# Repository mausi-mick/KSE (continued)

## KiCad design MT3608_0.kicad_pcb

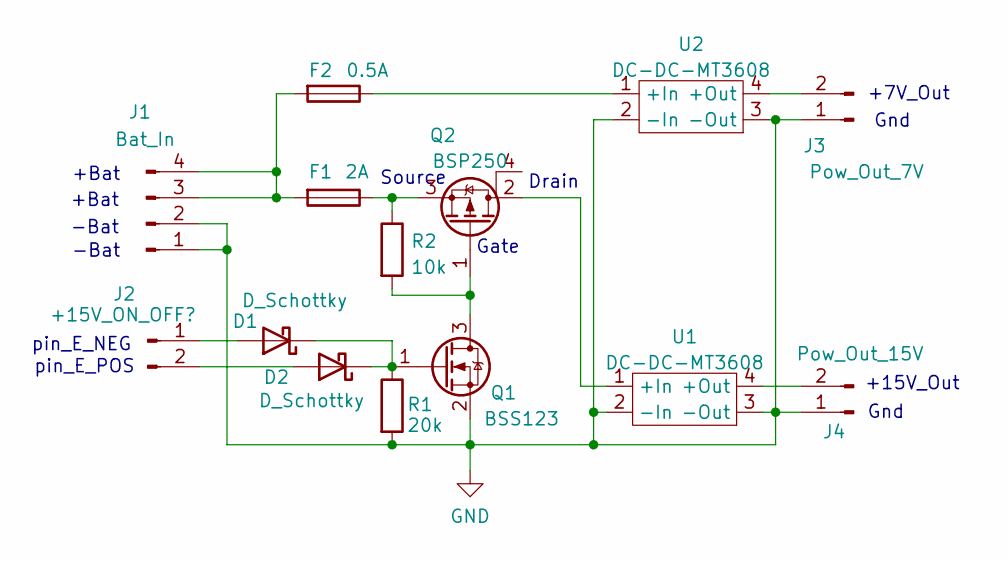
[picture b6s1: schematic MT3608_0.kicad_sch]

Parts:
D1, D2: D_Schottky; D_0805_2012Metric_Pad1.15x1.40mm_HandSolder
F1: 2A; Fuse_1206_3216Metric_Pad1.42x1.75mm_HandSolder
F2: 0.5A; Fuse_1206_3216Metric_Pad1.42x1.75mm_HandSolder
J1: Bat_In; PinHeader_1x04_P2.54mm_Vertical
J2: +15V_ON_OFF?; PinHeader_1x02_P2.54mm_Vertical
J3: Pow_Out_7V; PinHeader_1x02_P2.54mm_Vertical
J4: Pow_Out_15V; PinHeader_1x02_P2.54mm_Vertical
Q1: BSS123; SOT-23
Q2: BSP250; SOT-223
R1: 20k; R_1206_3216Metric_Pad1.30x1.75mm_HandSolder
R2: 10k; R_1206_3216Metric_Pad1.30x1.75mm_HandSolder
U1, U2: DC-DC-MT3608

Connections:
GND: J1.1, J1.2, J3.1, J4.1, Q1.2 (S), R1.2, U1.2 (-In), U1.3 (-Out), U2.2 (-In), U2.3 (-Out)
unnamed: D1.2 (A), J2.1
unnamed: F1.1, Q2.3 (S), R2.1
unnamed: F1.2, F2.2, J1.3, J1.4
unnamed: F2.1, U2.1 (+In)
unnamed: D2.2 (A), J2.2
unnamed: J3.2, U2.4 (+Out)
unnamed: J4.2, U1.4 (+Out)
unnamed: D1.1 (K), D2.1 (K), Q1.1 (G), R1.1
unnamed: Q1.3 (D), Q2.1 (G), R2.2
unnamed: Q2.2 (D), U1.1 (+In)

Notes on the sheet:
Drain
-Bat
pin_E_NEG
Source
+Bat
pin_E_POS
+15V_Out
Gnd
Gate
+7V_Out

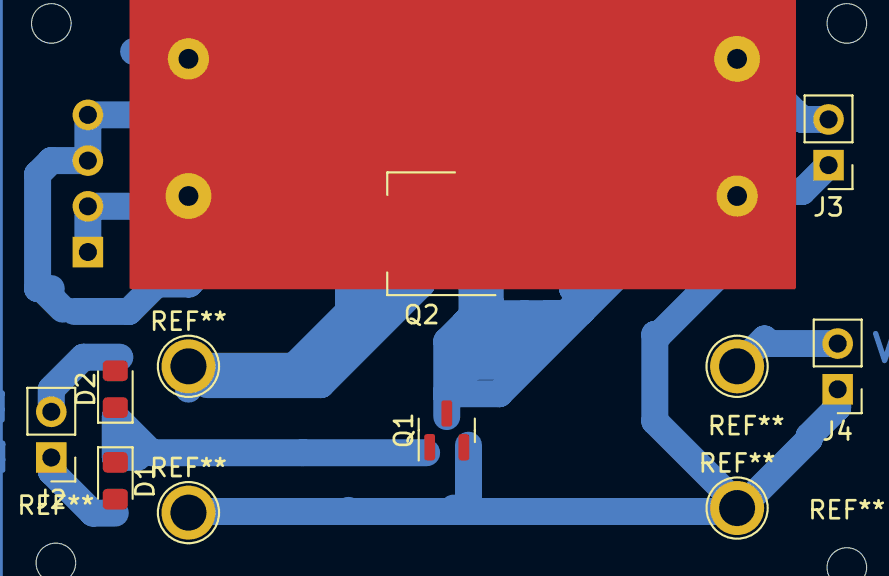
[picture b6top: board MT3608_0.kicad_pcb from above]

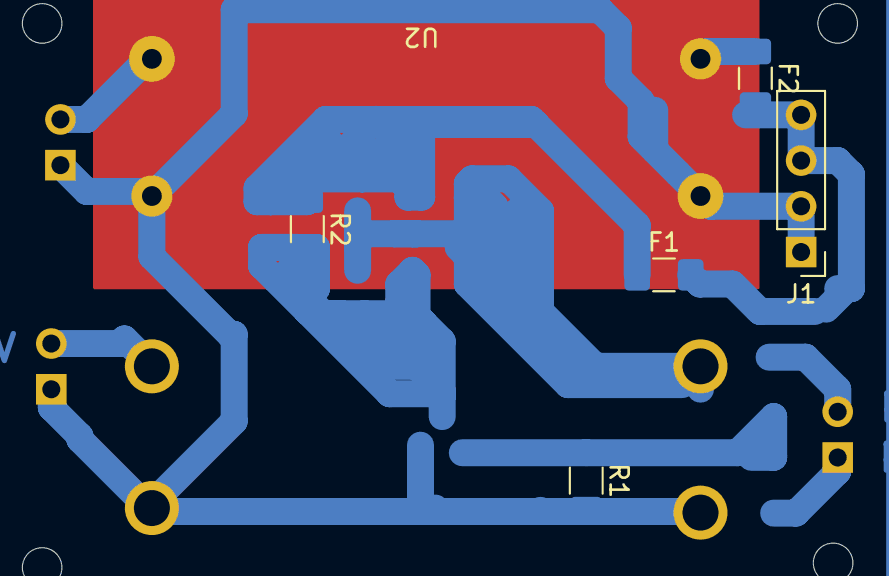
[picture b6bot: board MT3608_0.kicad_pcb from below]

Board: 2 copper layers, 13 parts (6 on the bottom side), 9 nets.
